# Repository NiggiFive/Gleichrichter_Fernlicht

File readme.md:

# Gleichrichter Fernlicht PCB#
Schaltung stammt von hier: https://fahrradzukunft.de/14/mosfet-gleichrichter
Serienkondensator von 390uF antiparallel hat sich als optimum herausgestellt (im Vgl. zu 330uF und 560uF)
Spannungsfestigkeit Kondensator: 35V (Großzügig)

Verwendete Mosfets:
N-Kanal: IRLML 0030
P-Kanal: TSM 3401 -> Kann aber nur max. 12V VGS

Anforderungen Mosfets:
möglichst niedriges RDS_on
30V VDSmax (großzügig)
Am besten möglichst hohes VGS_max -> 20V
Gate-Source sieht immer ca. die Ausgangsspannung -> 12V Reichen locker für 2 LEDs in Reihe mit jew. 6V am Ausgang. Je höhere Ausgangsspannungen auftreten können desto höher muss VGS_max sein.

Zenerdioden Schützen Gate vor zu hohen Spannungen. Aber auch nur kurzfristig, denn die können den Strom nicht ab. Zenerspannungen sollten also unter dem VGS_max sein!

Bei erster Version war Fehler im Layout: Die Pin-Reihenfolge der Standard-Mosfet-Symbole passt nicht zum SOT-23 Gehäuse.
Mosfets mussten daher auf dem Kopf gelötet werden.
Funktioniert so aber gut.

Ist jetzt im Schaltplan korrigiert aber das Layout  noch nicht fertig. (Falls nochmal aufgebaut wird)

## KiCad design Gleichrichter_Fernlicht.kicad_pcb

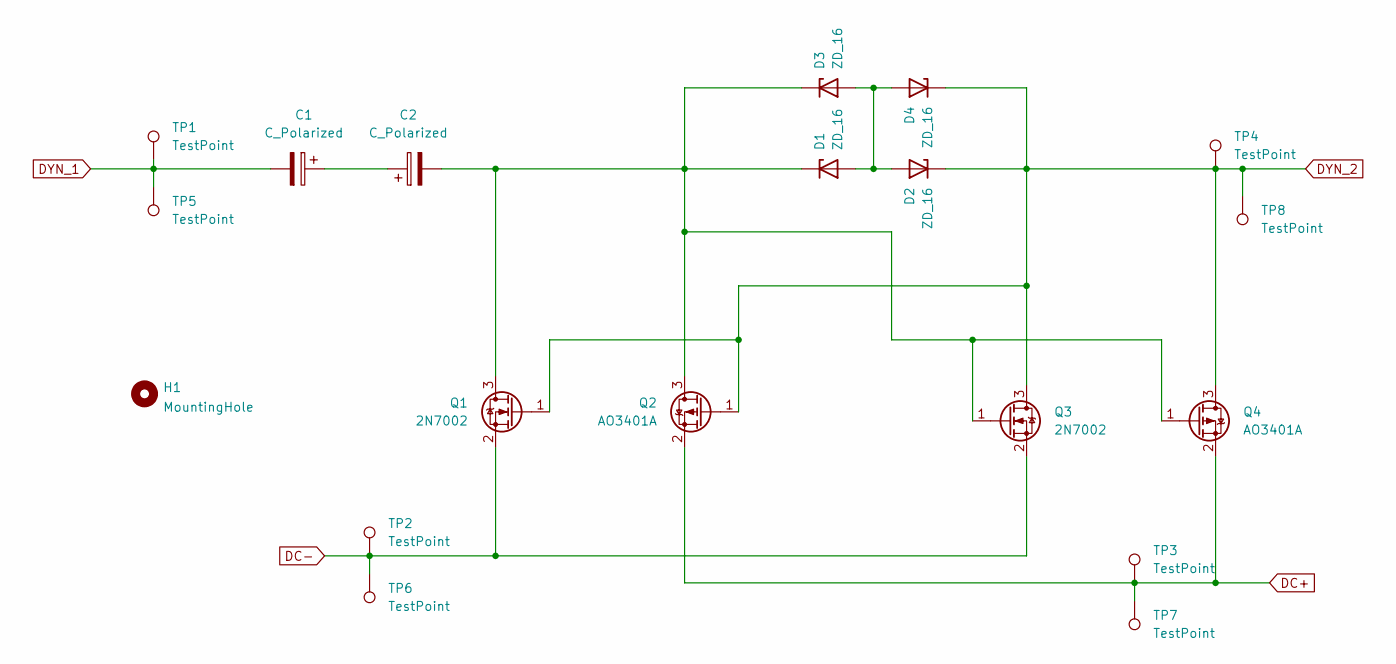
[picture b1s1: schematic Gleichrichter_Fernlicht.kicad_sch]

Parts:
C1, C2: C_Polarized; CP_Elec_10x10.5
D1, D2: ZD_16; D_SOD-123
D3, D4: ZD_16; D_MiniMELF_Handsoldering
H1: MountingHole; MountingHole_5mm
Q1, Q3: 2N7002; SOT-23_Handsoldering
Q2, Q4: AO3401A; SOT-23_Handsoldering
TP1, TP2, TP3, TP4, TP5, TP6, TP7, TP8: TestPoint; TestPoint_Pad_2.5x2.5mm

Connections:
DC+: Q2.2 (S), Q4.2 (S), TP3.1, TP7.1
DC-: Q1.2 (S), Q3.2 (S), TP2.1, TP6.1
DYN_1: C1.2, TP1.1, TP5.1
DYN_2: D2.1 (K), D4.1 (K), Q1.1 (G), Q2.1 (G), Q3.3 (D), Q4.3 (D), TP4.1, TP8.1
unnamed: C1.1, C2.1
unnamed: D1.2 (A), D2.2 (A), D3.2 (A), D4.2 (A)
unnamed: C2.2, D1.1 (K), D3.1 (K), Q1.3 (D), Q2.3 (D), Q3.1 (G), Q4.1 (G)

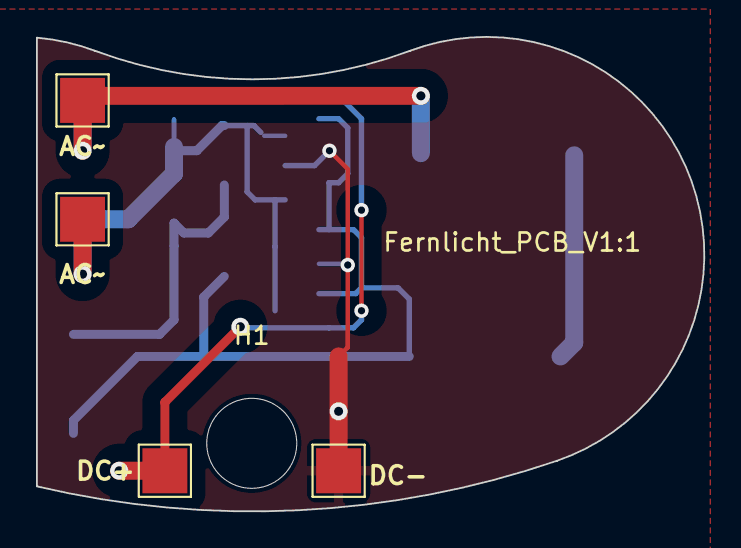
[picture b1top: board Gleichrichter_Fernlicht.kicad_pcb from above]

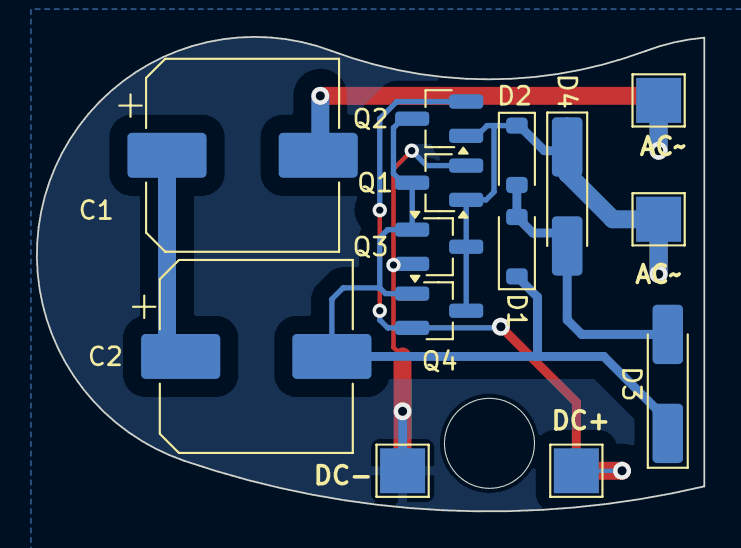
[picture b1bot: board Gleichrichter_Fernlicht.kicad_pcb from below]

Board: 2 copper layers, 37.1 x 26.4 mm, 19 parts (14 on the bottom side), 7 nets.

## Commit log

2022-02-08 Schaltplan gezeichnet und Bauteile platziert
2022-02-10 Dateien fuer Leiterplattenumriss von Jan hinzugefuegt
2022-02-10 Kontur von Jan importiert und gelayoutet. Evtl. noch Kupferflaechen machen?
2022-02-17 Stand der zu jlcpcb geschickt wurde
2022-04-24 Standard Mosfet-Symbol hat nicht zu SOT-23 Footprint gepasst. (Drain und Source vertauscht). Jetzt korrigiert. Layout noch nicht fertig. Hotfix: Transistoren auf erster Platine verkehrt herum drauflö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
2022-04-24 readme hinzugefuegt
2025-12-28 update: Layout korrigiert und an jlc geschickt
